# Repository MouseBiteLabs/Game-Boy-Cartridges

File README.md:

# Game Boy Cartridge Circuit Boards

This is a repository listing all of my Game Boy game circuit board variants.

## Game Boy Board Links

| **Board Name**       | **Board Number**   | **Max ROM Size**       | **Max RAM Size**  | **Multicart Support?** | **Memory Family Used**          |
|----------------------|--------------------|------------------------|-------------------|------------------------|---------------------------------|
| MBC1 (Type B)        | GB-4DV4S-01B       | 4 MB                   | 32 KB             | No                     | Type B (29F016, 29F032, 29F033) |
| MBC3 (Type B)        | GB-4KV4S-01B       | 4 MB                   | 32 KB             | No                     | Type B (29F016, 29F032, 29F033) |
| MBC5 (Type B)        | GB-4AV8S-01B       | 4 MB                   | 128 KB            | No                     | Type B (29F016, 29F032, 29F033) |
| MBC3 Multicart       | GB-4KV8S-01B       | 4 MB (2x 2 MB, 4x 1MB) | 128 KB (4x 32 KB) | Yes                    | Type B (29F032, 29F033)         |
| MBC5 Multicart       | GB-4AV8S-01B       | 4 MB (2x 2 MB, 4x 1MB) | 128 KB (4x 32 KB) | Yes                    | Type B (29F032, 29F033)         |
| MBC1 (Type A)        | GB-2DV4S-01A       | 2 MB                   | 32 KB             | No                     | Type A (M29F160)                |
| MBC3 (Type A)        | GB-2KV4S-01A       | 2 MB                   | 32 KB             | No                     | Type A (M29F160)                |
| MBC5 (Type A)        | GB-2AV8S-01A       | 2 MB                   | 128 KB            | No                     | Type A (M29F160)                |
| MBC1 (Type A, FRAM)  | GB-2DF4S-01A       | 2 MB                   | 32 KB             | No                     | Type A (M29F160)                |
| MBC3 (Type A, FRAM)  | GB-2KF4S-01A       | 2 MB                   | 32 KB             | No                     | Type A (M29F160)                |
| MBC5 (Type A, FRAM)  | GB-2AF4S-01A       | 2 MB                   | 32 KB             | No                     | Type A (M29F160)                |

## Naming Convention

| GB       | \- | 2                 | A               | V              | 4            | S                                            | \- | 01       | A                                       |
| -------- | -- | ----------------- | --------------- | -------------- | ------------ | -------------------------------------------- | -- | -------- | --------------------------------------- |
| Game Boy |    | Max ROM Size (MB) | Mapper Chip     | SRAM or FRAM?  | Max RAM Size | Multicart Support                            |    | Revision | Memory Family                           |
|          |    | 1                 | N = None        | X = None       | 0 = None     | S = Single game                              |    |          | A = New EEPROM (M29F160)                |
|          |    | 2                 | D = MBC1        | V = SRAM       | 1 = 2 KB     | D = Multicart (2x, split max ROM/RAM space)  |    |          | B = NOS EEPROM (29F016, 29F032, 29F033) |
|          |    | 4                 | K = MBC3        | F = FRAM       | 2 = 8 KB     | Q = Multicart (4x, split max ROM/RAM space)  |    |          |                                         |
|          |    | 6                 | A = MBC5        |                | 4 = 32 KB    |                                              |    |          |                                         |
|          |    | 8                 |                 |                | 8 = 128 KB   |                                              |    |          |                                         |

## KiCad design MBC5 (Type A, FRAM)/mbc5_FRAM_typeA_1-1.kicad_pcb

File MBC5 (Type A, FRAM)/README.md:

# Game Boy MBC5 Cartridge - Type A, FRAM

This is an alternate design of my <a href="https://github.com/MouseBiteLabs/Game-Boy-Cartridges/tree/main/MBC5%20(Type%20A%2C%20SRAM)">flashable MBC5-based cartridge for the Game Boy</a>. This board uses non-volatile FRAM instead of SRAM to hold save data. I made this specifically for use with the <a href="https://github.com/MouseBiteLabs/Super-Game-Boy-Plus/tree/main">Super Game Boy Plus boards.</a>

**This MBC5 cartridge uses brand new M29F160 EEPROM chips and non-volatile FRAM.**

This circuit board should cover most MBC5 games, and is able to make games up to 2 MB in size, that use up to 256 Kbit of RAM. It is fully compatible with both the <a href="https://www.gbxcart.com/">GBxCart RW</a> and sanni's <a href="https://github.com/sanni/cartreader">Open Source Cart Reader (OSCR)</a> so you can transfer games and save files to and from the board. Because of the FRAM this board utilizes, <a href="https://github.com/MouseBiteLabs/Game-Boy-Cartridges/tree/main/MBC5%20(Type%20A%2C%20SRAM)#why-not-fram">it is technically only fully compatible with regular Game Boy games, and not Game Boy Color games,</a> though no issues have been reported in the past when using them with Game Boy Color games.

All gerbers and source files can be found in this repo, as this project is fully open source.

## Important Things Before You Start

1) To use this board, you need to have an original Game Boy game that uses an MBC5 mapper chip. <a href="https://catskull.net/gb-rom-database/">You can find a list of games and their mappers here</a>. Use the search function. Please note the RAM is in bytes, not bits. Since RAM in this repo is defined in bits, you need to convert by multiplying the number of bytes by 8.
2) You will need to remove the MBC5 from your donor cartridge for use on this board. This will require a hot air rework station or a hot plate. There's a list below of other parts you can re-use from the donor cartridge.
3) When soldering parts on, it's a good idea to put kapton tape or otherwise cover the bottom cartridge edge. You do not want to get solder on the cartridge contacts.
4) I am not responsible for any damage you do to your self or your property. Attempt this project at your own risk.
5) I do not guarantee design compatibility. You may encounter issues with certain games. There is also a chance I have made an error in the design or the BOM - if this is the case, I will do everything I can to address the problem as quickly as possible.
6) If you are using this board to make games other than for personal use, you must have permission from the originator to use and distribute any ROM images or other related material. You are responsible for making sure you adhere to any license requirements.

DO NOT use my circuit boards for profiting from stolen work - this especially includes homebrew content, ROM hacks, and using fan-made labels without permission from the originator. **Support original creators!**

## Board Characteristics and Order Information

The zipped folder contains all the gerber files for this board. The following options **must** be chosen when ordering boards for yourself.

- Thickness: 0.8mm
- Surface Finish: ENIG
- Gold Fingers: Yes, 30° chamfer

You can use the zipped folder at any board fabricator you like. You may also buy the board from PCBWay using this link (disclosure: I receive 10% of the sale value to go towards future PCB orders of my own):

<a href="https://oshpark.com/shared_projects/4iVMHuUe">The board is also listed on OSH Park as well.</a> **Be sure to get them in 0.8mm thickness if you order from here.**

## Required Equipment

The EEPROM on the board needs to be programmed somehow. There are a few options for doing this:

1) <a href="https://www.gbxcart.com/">**GBxCart**</a>. This is a perfect option if you want an easy way to make Game Boy cartridges without a lot of extra effort. This is a standalone flasher that plugs into your computer via USB. The cartridge circuit board is fully compatible with it, and it makes reflashing games extremely easy using <a href="https://github.com/lesserkuma/FlashGBX">lesserkuma's FlashGBX software</a>.
2) <a href="https://github.com/sanni/cartreader">**OSCR**</a> by sanni. This is the Open Source Cart Reader, capable of making backups of both the ROM and RAM contents of cartridges across many different systems - like the NES, SNES, Genesis, and of course Game Boy and Game Boy Advance. And you can also use it to flash these Game Boy cartridges. The OSCR however requires assembly (or someone to assemble it for you) and is a bit more cumbersome to interface with on a PC, but it's an extremely powerful tool that I can't recommend enough if you want to expand past Game Boys.
3) At the lowest level, you can buy an EEPROM programmer with a TSOP chip programming adapter. The downside to this method is that you have to desolder the chip every time you want to program it. The <a href="https://flashcatusb.com/">FlashcatUSB</a> is one popular option in retro spaces, but I use the <a href="https://xgecu.myshopify.com/products/xgecu-new-t48-tl866-3gprogrammer-v12-01-support-28000-ics-for-spi-nor-nand-flash-emmc-bga153-162-169-100-221-tsop-sop-plcc">T48 programmer</a> with the <a href="https://xgecu.myshopify.com/products/100-original-xgecu-adp_f48_ex-1-tsop48-special-adapter-for-nor-flash-only-use-on-t48-tl866-3g-programmer">TSOP48 adapter</a>.

### How to Program the Cartridges

<a href="https://github.com/MouseBiteLabs/Game-Boy-Cartridges/wiki">Check out the wiki for more information.</a>

## Board Fitment

The shape of this board was originally meant to mimic original Game Boy circuit boards as closely as possible. Unfortunately, when placed in some aftermarket Game Boy cartridge shells (like those from Cloud Game Store), the circuit board has a lot of freedom to rotate around the main screw hole in the bottom-middle of the cartridge. This can cause misalignment when you put it in a Game Boy, which can cause a game to either not load properly (garbled Game Boy logo) or shut off the Game Boy because of a short circuit. This isn't *dangerous* or anything, just annoying.

In order to make the boards fit nicer in any kind of shell, I added extended tabs of circuit board material to the edges of the cartridges to keep it from rotating too much in shells, which was suggested to me by <a href="https://github.com/orangeglo">orangeglo</a>! (Thanks!)

If you're having trouble fitting the circuit board into a shell, because the tabs interfere with the cart edges, you can safely sand or trim them down as there is no copper within the tabs themselves. The only shell that appears to require any kind of trimming are Kitsch-Bent shells.

## Bill of Materials (BOM)

| Reference | Value/Part Number | Package | Description      | Source                                           |
| --------- | ----------------- | ------- | ---------------- | ------------------------------------------------ |
| C19       | 0.1u              | 0603    | Capacitor (MLCC) | [https://mou.sr/3ENc15O](https://mou.sr/3ENc15O) |
| C20       | 0.1u              | 0603    | Capacitor (MLCC) | [https://mou.sr/3ENc15O](https://mou.sr/3ENc15O) |
| C21       | 0.1u              | 0603    | Capacitor (MLCC) | [https://mou.sr/3ENc15O](https://mou.sr/3ENc15O) |
| C22       | 0.1u              | 0603    | Capacitor (MLCC) | [https://mou.sr/3ENc15O](https://mou.sr/3ENc15O) |
| R17       | 10k               | 0603    | Resistor         | [https://mou.sr/3riR7IH](https://mou.sr/3riR7IH) |
| U7        | M29F160           | TSOP-48 | Flash EEPROM     | [https://mou.sr/3MNWQ0b](https://mou.sr/3MNWQ0b) |
| U8        | MBC5              | QFP-32  | MBC5 Mapper      | Donor Game Boy Game                              |
| U9        | FM18W08-SG        | SOIC-28 | FRAM             | [https://mou.sr/4cRIJlb](https://mou.sr/4cRIJlb) |
| U10       | SN74LVC1G332      | SOT-363 | 3-input Or Gate  | [https://mou.sr/3XdbXoN](https://mou.sr/3XdbXoN) |

## Labels

If you want a Bucket Mouse branded label for your cartridge, look no further than <a href="https://krizdingus.com/mousebitelabs/">krizdingus's designs</a>. Special thanks to Kris for designing these, they look awesome! (If you are going to order/print these, use the high-res images hosted on his website, and *keep the labels for personal or non-commercial use only.*)

## Revision History

### v1.1
- Fix board number and update silkscreen for consistency

### v1.0
- Initial revision

## Resources and Acknowledgements

- <a href="http://www.devrs.com/gb/files/hardware.html">Jeff Frohwein's GameBoy Tech Page</a>
- <a href="https://gbhwdb.gekkio.fi/">Game Boy Hardware Database</a>
- <a href="https://catskull.net/gb-rom-database/">Nintendo Gameboy Game List</a>
- <a href="https://www.gbxcart.com/">insideGadgets discord server for GBxCart RW compatibility requirements</a>
- <a href="https://github.com/lesserkuma/FlashGBX">Lesserkuma's FlashGBX software</a>
- <a href="https://github.com/sanni/cartreader">sanni's Open Source Cart Reader (OSCR)</a>, and thanks to the OSCR discord server for help and feedback
- Board outline modified from <a href="https://tinkerer.us/projects/homebrew-gameboy-cartridge.html">Dillon Nichols's Homebrew Gameboy Cartridge project</a>
- Thanks to <a href="https://github.com/orangeglo">orangeglo</a> for his suggestion of adding spacers around the board edge for better fitment in aftermarket cartridges
- Some components from <a href="https://github.com/adafruit/Adafruit-Eagle-Library">Adafruit's Eagle parts library</a>
- Some components from <a href="https://www.snapeda.com/">SnapMagic</a>
- Thank you to <a href="https://github.com/Gekkio">gekkio</a> for their deep Game Boy knowledge resources, and for collaboration in demystifying some of the design choices on Game Boy cartridges

## License

<br />This work is licensed under a <a rel="license" href="http://creativecommons.org/licenses/by-sa/4.0/">Creative Commons Attribution-ShareAlike 4.0 International License</a>. You are able to copy and redistribute the material in any medium or format, as well as remix, transform, or build upon the material for any purpose (even commercial) - but you **must** give appropriate credit, provide a link to the license, and indicate if any changes were made.

©MouseBiteLabs 2025

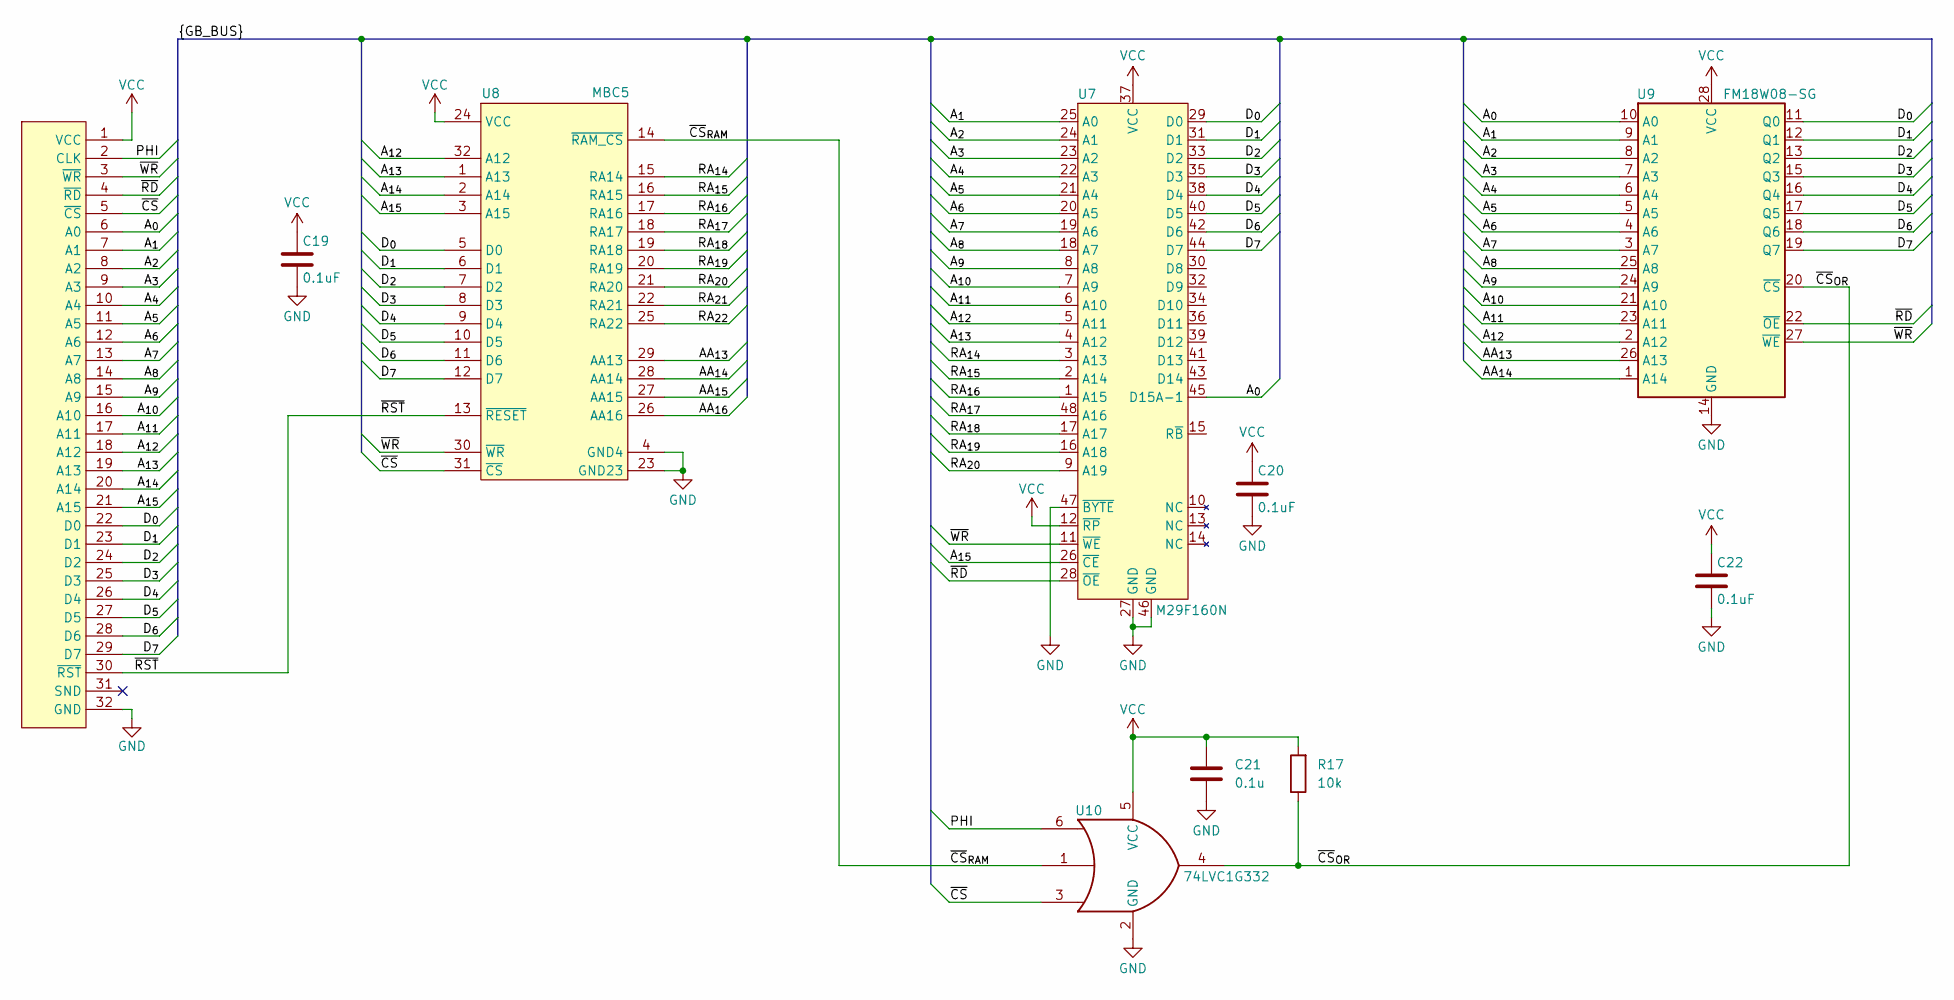
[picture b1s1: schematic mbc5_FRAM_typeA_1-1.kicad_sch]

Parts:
C19, C20, C22: 0.1uF; C_0603_1608Metric_Boxed
C21: 0.1u; C_0603_1608Metric_Boxed
P1: GBC_CARTTAB; GBC_CART_TABBED
R17: 10k; R_0603_1608Metric_Boxed
U7: M29F160N; TSOP-I-48_18.4x12mm_P0.5mm
U8: MBC5; QFP-32
U9: FM18W08-SG; SO28
U10: 74LVC1G332; SOT-363_SC-70-6

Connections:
/AA_{13}: U8.29 (AA13), U9.26 (A13)
/AA_{14}: U8.28 (AA14), U9.1 (A14)
/AA_{15}: U8.27 (AA15)
/AA_{16}: U8.26 (AA16)
/A_{0}: P1.6 (A0), U7.45 (D15A-1), U9.10 (A0)
/A_{1}: P1.7 (A1), U7.25 (A0), U9.9 (A1)
/A_{2}: P1.8 (A2), U7.24 (A1), U9.8 (A2)
/A_{3}: P1.9 (A3), U7.23 (A2), U9.7 (A3)
/A_{4}: P1.10 (A4), U7.22 (A3), U9.6 (A4)
/A_{5}: P1.11 (A5), U7.21 (A4), U9.5 (A5)
/A_{6}: P1.12 (A6), U7.20 (A5), U9.4 (A6)
/A_{7}: P1.13 (A7), U7.19 (A6), U9.3 (A7)
/A_{8}: P1.14 (A8), U7.18 (A7), U9.25 (A8)
/A_{9}: P1.15 (A9), U7.8 (A8), U9.24 (A9)
/A_{10}: P1.16 (A10), U7.7 (A9), U9.21 (A10)
/A_{11}: P1.17 (A11), U7.6 (A10), U9.23 (A11)
/A_{12}: P1.18 (A12), U7.5 (A11), U8.32 (A12), U9.2 (A12)
/A_{13}: P1.19 (A13), U7.4 (A12), U8.1 (A13)
/A_{14}: P1.20 (A14), U8.2 (A14)
/A_{15}: P1.21 (A15), U7.26 (~CE), U8.3 (A15)
/D_{0}: P1.22 (D0), U7.29 (D0), U8.5 (D0), U9.11 (Q0)
/D_{1}: P1.23 (D1), U7.31 (D1), U8.6 (D1), U9.12 (Q1)
/D_{2}: P1.24 (D2), U7.33 (D2), U8.7 (D2), U9.13 (Q2)
/D_{3}: P1.25 (D3), U7.35 (D3), U8.8 (D3), U9.15 (Q3)
/D_{4}: P1.26 (D4), U7.38 (D4), U8.9 (D4), U9.16 (Q4)
/D_{5}: P1.27 (D5), U7.40 (D5), U8.10 (D5), U9.17 (Q5)
/D_{6}: P1.28 (D6), U7.42 (D6), U8.11 (D6), U9.18 (Q6)
/D_{7}: P1.29 (D7), U7.44 (D7), U8.12 (D7), U9.19 (Q7)
/PHI: P1.2 (CLK), U10.6
/RA_{14}: U7.3 (A13), U8.15 (RA14)
/RA_{15}: U7.2 (A14), U8.16 (RA15)
/RA_{16}: U7.1 (A15), U8.17 (RA16)
/RA_{17}: U7.48 (A16), U8.18 (RA17)
/RA_{18}: U7.17 (A17), U8.19 (RA18)
/RA_{19}: U7.16 (A18), U8.20 (RA19)
/RA_{20}: U7.9 (A19), U8.21 (RA20)
/RA_{21}: U8.22 (RA21)
/RA_{22}: U8.25 (RA22)
/~CS: P1.5 (~CS), U8.31 (~CS), U10.3
/~CS_{OR}: R17.1, U9.20 (~CS), U10.4
/~CS_{RAM}: U8.14 (~RAM_CS), U10.1
/~RD: P1.4 (~RD), U7.28 (~OE), U9.22 (~OE)
/~RST: P1.30 (~RST), U8.13 (~RESET)
/~WR: P1.3 (~WR), U7.11 (~WE), U8.30 (~WR), U9.27 (~WE)
GND: C19.2, C20.2, C21.2, C22.2, P1.32 (GND), U7.27 (GND), U7.46 (GND), U7.47 (~BYTE), U8.4 (GND4), U8.23 (GND23), U9.14 (GND), U10.2 (GND)
VCC: C19.1, C20.1, C21.1, C22.1, P1.1 (VCC), R17.2, U7.12 (~RP), U7.37 (VCC), U8.24 (VCC), U9.28 (VCC), U10.5 (VCC)

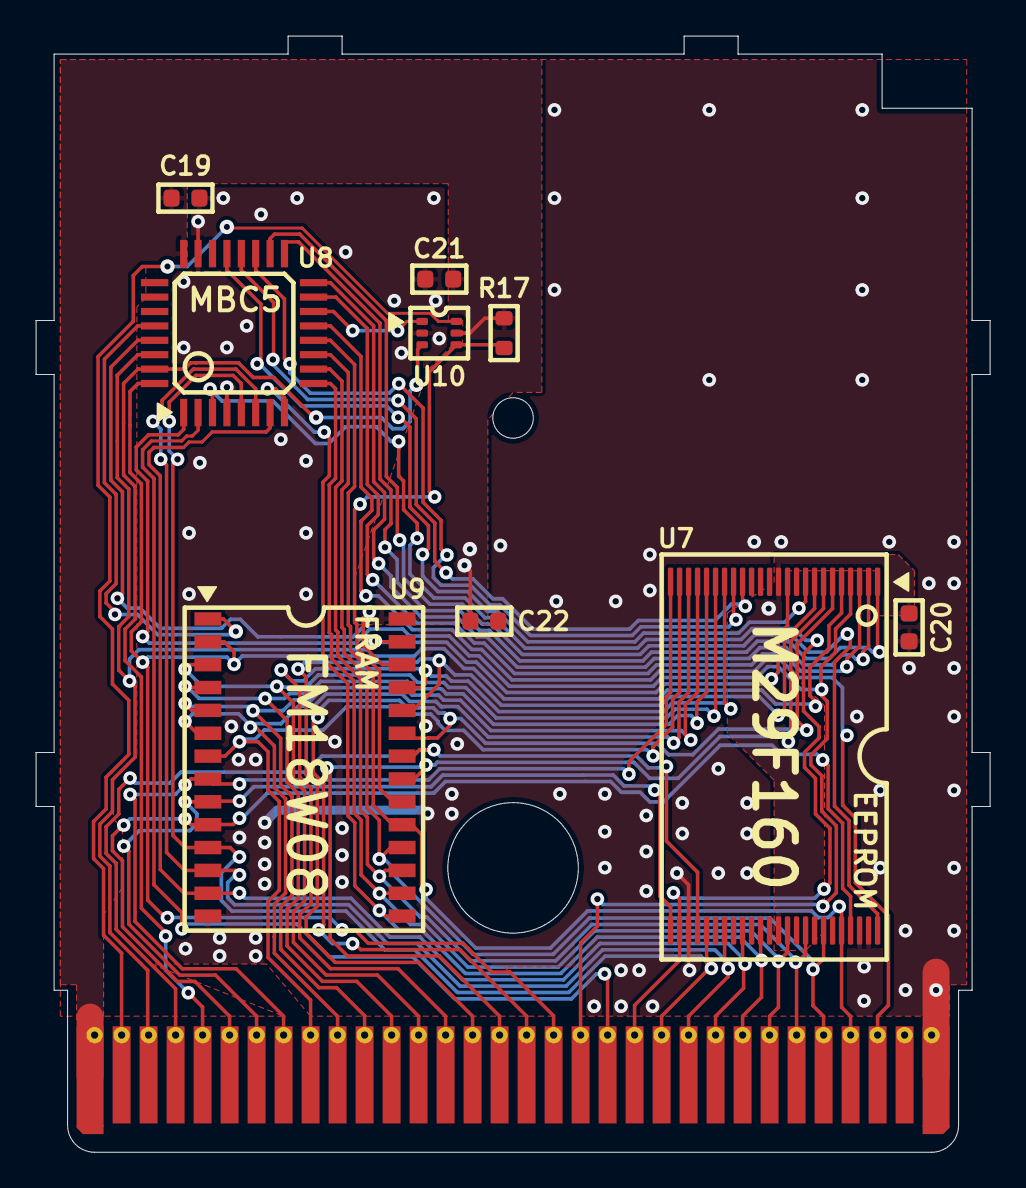
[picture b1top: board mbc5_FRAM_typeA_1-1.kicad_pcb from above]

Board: 2 copper layers, 53.0 x 62.0 mm, 10 parts (0 on the bottom side), 42 nets.

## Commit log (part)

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2024-10-07 Create MBC3 (Type A, SRAM)

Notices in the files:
MBC5 (Type A, FRAM)/README.md:
This work is licensed under a Creative Commons Attribution-ShareAlike 4.0 International License. You are able to copy and redistribute the material in any medium or format, as well as remix, transform, or build upon the material for any purpose (even commercial) - but you **must** give appropriate credit, provide a link t
©MouseBiteLabs 2025
